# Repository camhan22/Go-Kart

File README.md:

# Go-Kart
Electric Go-Kart using 12V FIRST robotics CIM Motors

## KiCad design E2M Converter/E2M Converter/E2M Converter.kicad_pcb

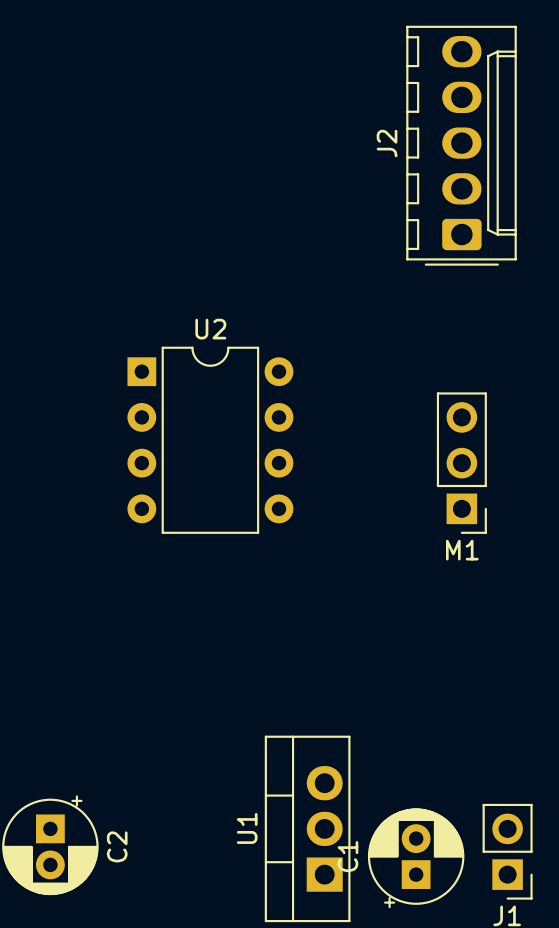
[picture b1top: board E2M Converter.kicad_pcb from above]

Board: 2 copper layers, 7 parts (0 on the bottom side), 7 nets, no tracks yet.

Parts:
C1, C2: 1uF; CP_Radial_D5.0mm_P2.00mm
J1: Input Connector; PinHeader_1x02_P2.54mm_Vertical
J2: Conn_01x05; Molex_KK-254_AE-6410-05A_1x05_P2.54mm_Vertical
M1: Motor_Servo; PinHeader_1x03_P2.54mm_Vertical
U1: L7805 TO220; TO-220-3_Vertical
U2: ATtiny85-20PU; DIP-8_W7.62mm

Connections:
+5V: C2.1, M1.2, U1.3, U2.8
+12V: C1.1, J1.1, U1.1
GND: C1.2, C2.2, J1.2, J2.5, M1.3, U1.2, U2.4
MISO: J2.2, M1.1, U2.6
RESET: J2.4, U2.1
SCL-SCK: J2.1, U2.7
SDA-MOSI: J2.3, U2.5

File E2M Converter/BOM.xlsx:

Schematic Annotation | Part Number | Description | Qty | Price | Supplier | Total Cost | Link
U2 | ATTINY85-20PU-ND | AVR series Microcontroller IC 8-Bit 20MHz 8KB (4K x 16) FLASH 8-PDIP | 1 | 1.45 | Digikey | 1.45 | https://www.digikey.com/en/products/detail/microchip-technol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
U1 | 497-2947-5-ND | Linear Voltage Regulator IC Positive Fixed 1 Output 1.5A TO-220AB | 1 | 0.54 | Digikey | 0.54 | https://www.digikey.com/en/products/detail/stmicroelectronic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
J1 | 277-6156-ND | 2 Position Wire to Board Terminal Block 45° (135°) Angle with Board 0.098" (2.5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 | 1 | 0.31 | Digikey | 0.31 | https://www.digikey.com/en/products/detail/phoenix-contact/1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
J2 | 23-0022292051-ND | Connector Header Through Hole 5 position 0.100" (2.54mm) | 1 | 1.43 | Digikey | 1.43 | https://www.digikey.com/en/products/detail/molex/0022292051/1130591
J2 Mate | 23-0010112053-ND | 5 Rectangular Connectors - Housings Receptacle White 0.100" (2.54mm) | 1 | 0.28999999999999998 | Digikey | 0.28999999999999998 | https://www.digikey.com/en/products/detail/molex/0010112053/171981
J2 Crimps | WM3724CT-ND | Socket Contact Tin 22-28 AWG Crimp - | 5 | 0.12 | Digikey | 0.6 | https://www.digikey.com/en/products/detail/molex/0008700056/2421861
C1,C2 | 732-8851-1-ND | 1 µF 50 V Aluminum Electrolytic Capacitors Radial, Can - 2000 Hrs @ 105°C | 2 | 0.1 | Digikey | 0.2 | https://www.digikey.com/en/products/detail/w%C3%BCrth-elektr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
M2 | 102-5593-ND | Fan Tubeaxial 12VDC Square - 40mm L x 40mm H omniCOOL™ Magnetic Sleeve 5.5 CFM 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 | 1 | 5.57 | Digikey | 5.57 | https://www.digikey.com/en/products/detail/cui-devices/CFM-4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
Heatsink | HS106-ND | Heat Sink TO-220 Aluminum 3.0W @ 80°C Board Level | 1 | 0.33 | Digikey | 0.33 | https://www.digikey.com/en/products/detail/aavid-thermal-div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
Heatsink Bolt | 91274A102 | Zinc-Aluminum-Coated Alloy Steel Socket Head Screw | 1 | 5.38 | Mcmaster Carr | 5.38 | https://www.mcmaster.com/91274A102/
Heatsink Nut | 90592A085 | Steel Hex Nut | 1 | 1.17 | Mcmaster Carr | 1.17 | https://www.mcmaster.com/90592A085/
Servo Motor | 1528-1083-ND | Positional Rotation DC Motor Servomotor, RC (Hobby) - - - 5VDC | 1 | 19.95 | Digikey | 19.95 | https://www.digikey.com/en/products/detail/adafruit-industri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
Throttle Cable | B071VPYPD7 | 82 Inch Go Kart Throttle Cable Line Wire For 150CC 250CC Carter Throttle Cable 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 | 1 | 9.5 | Amazon.com | 9.5 | Amazon.com: 82 Inch Go Kart Throttle Cable Line Wire For 150CC 250CC Carter Thr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
 |  |  |  |  | Total Cost | 46.72

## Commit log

2021-06-14 Add Files
2021-06-14 Created a references file
2021-06-15 Added Schematic
2021-06-15 Added annotations to schematic
2021-06-15 Added Throttle controller code
2021-06-20 Changed stuff
    Added a throttle tester.
    Added the wiring schematic for the whole kart and updated schematics for throttle
2021-06-20 Added status codes
2021-06-23 Updated STL parts
2021-06-24 ggfh
2021-06-24 Changed scaling
    Changed how the scaling is input inside the map function. Now, the min and max values are based off measured values. May add code to update these limits as heat will change these values. This was som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
2021-06-24 Added voltage scaling to system
2021-06-25 Made the throttle calibrate itself on startup
2021-06-26 Updated throttle body.stl to include physical stops due to potentiometer not able to read at its mechanical stops
2021-06-29 E2M Converter created
    Created a system to convert the electrical throttle to an electrical signal to work with briggs and stratton 192402 motor that can be used instead of electric system
2021-07-01 Updated and verified model
2021-07-01 Added modeling files
2021-07-08 Added code to main controller
2021-08-14 Updated schematic and code
    Added pulldown resistor instead of direct grounding on MOSI line due to not being able to program it.
    Also added EEPROM code to store the calibration to not have to calibrate each time at startup. Calibration can be forced if the throttle is in the full on position when in the normal orientation
2021-10-11 ifsdif
